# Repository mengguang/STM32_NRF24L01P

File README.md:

# STM32_NRF24L01P
NRF24L01P Development board with STM32F030F4 MCU

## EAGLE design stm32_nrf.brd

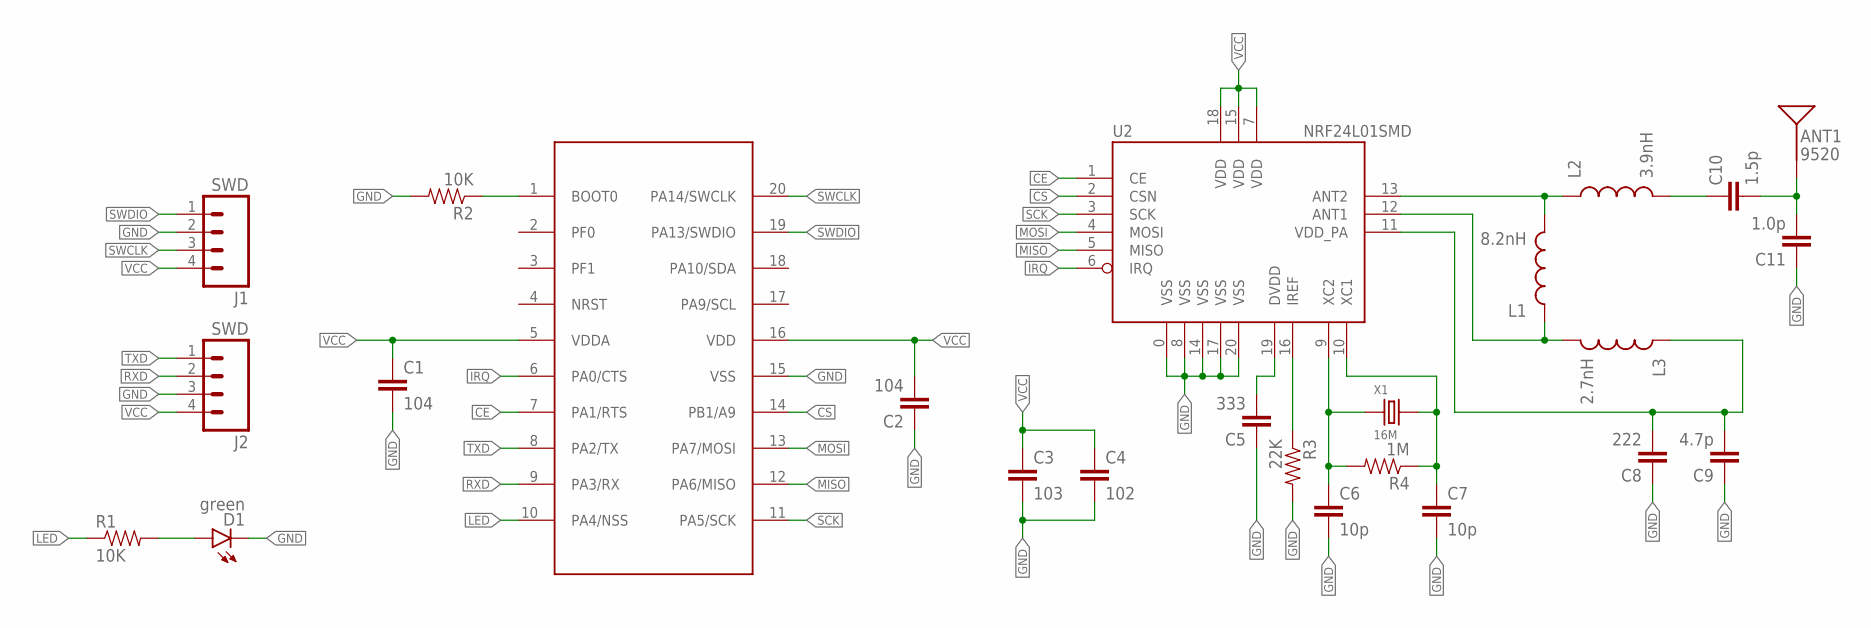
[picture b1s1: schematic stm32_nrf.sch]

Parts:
ANT1: 9520; ANT-2.4GHZ-9.5X2.0MM
C1, C2: 104; 0402-CAP
C3: 103; 0402-CAP
C4: 102; 0402-CAP
C5: 333; 0402-CAP
C6, C7: 10p; 0402-CAP
C8: 222; 0402-CAP
C9: 4.7p; 0402-CAP
C10: 1.5p; 0402-CAP
C11: 1.0p; 0402-CAP
D1: green; LED-0603-EASY
J1, J2: SWD; 1X04_NO_SILK
L1: 8.2nH; C0402
L2: 3.9nH; C0402
L3: 2.7nH; C0402
R1, R2: 10K; 0402-RES
R3: 22K; 0402-RES
R4: 1M; 0402-RES
U1: STM32F030F4; TSSOP20
U2: NRF24L01SMD; QFN20
X1: 16M; X4-SMD-3.2X2.5X0.7MM

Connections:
CE: U1.7 (PA1/RTS), U2.1 (CE)
CS: U1.14 (PB1/A9), U2.2 (CSN)
DVDD: C5.2, U2.19 (DVDD)
GND: C1.2, C2.1, C3.2, C4.2, C5.1, C6.2, C7.2, C8.1, C9.1, C11.1, D1.- (C), J1.2, J2.3, R2.2, R3.2, U1.15 (VSS), U2.0 (VSS), U2.8 (VSS), U2.14 (VSS), U2.17 (VSS), U2.20 (VSS)
IRQ: U1.6 (PA0/CTS), U2.6 (IRQ)
LED: R1.1, U1.10 (PA4/NSS)
MISO: U1.12 (PA6/MISO), U2.5 (MISO)
MOSI: U1.13 (PA7/MOSI), U2.4 (MOSI)
unnamed: C7.1, R4.1, U2.10 (XC1), X1.3 (2)
unnamed: C6.1, R4.2, U2.9 (XC2), X1.1
unnamed: L1.2, L2.1, U2.13 (ANT2)
unnamed: D1.+ (A), R1.2
unnamed: R2.1, U1.1 (BOOT0)
unnamed: C10.1, L2.2
unnamed: ANT1.FEED, C10.2, C11.2
unnamed: L1.1, L3.2, U2.12 (ANT1)
unnamed: R3.1, U2.16 (IREF)
RXD: J2.2, U1.9 (PA3/RX)
SCK: U1.11 (PA5/SCK), U2.3 (SCK)
SWCLK: J1.3, U1.20 (PA14/SWCLK)
SWDIO: J1.1, U1.19 (PA13/SWDIO)
TXD: J2.1, U1.8 (PA2/TX)
VCC: C1.1, C2.2, C3.1, C4.1, J1.4, J2.4, U1.5 (VDDA), U1.16 (VDD), U2.7 (VDD), U2.15 (VDD), U2.18 (VDD)
VDD_PA: C8.2, C9.2, L3.1, U2.11 (VDD_PA)

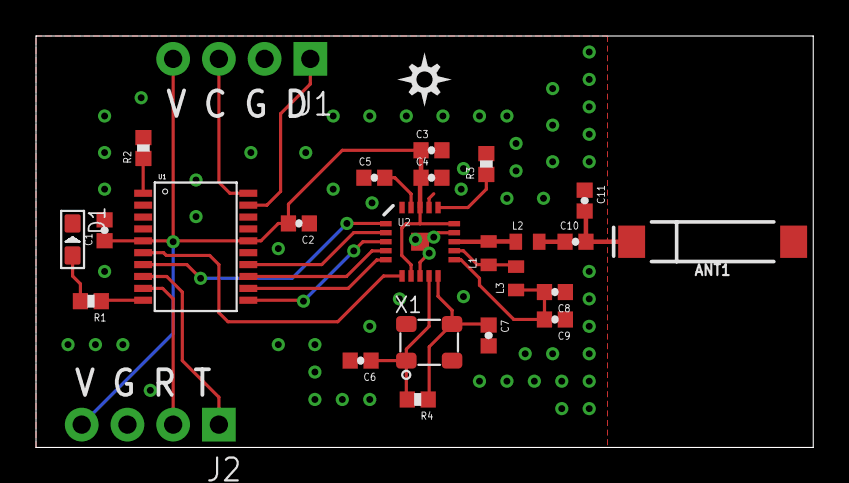
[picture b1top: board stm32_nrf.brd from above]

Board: 2 copper layers, 43.2 x 22.9 mm, 26 parts (0 on the bottom side), 24 nets.

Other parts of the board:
U$1: DIYNOVA_LOGO_SMALL

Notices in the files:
parts and their libraries:
SparkFun-Connectors: Licensing: Creative Commons ShareAlike 4.0 International - https://creativecommons.org/licenses/by-sa/4.0
